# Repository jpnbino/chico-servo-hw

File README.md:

# Chico - HW #

This is a fully working board which you may wanna use as reference or may clone and customize to your needs. The board was designed to an specific project which required ADC, PWM, SERIAL, and I/O connection.

Example firmware [**here**](https://bitbucket.org/jpnbino/fw_palhaservo/src/master/).

## PCB ##

### Board details ###

|  Item           |Description |
|-----------------|------------|
| Core            | PIC16LF1824|
| Input Voltage (Vin)   |  4.75V ≤ Vin ≤ 10V    |
| Board Size      | 16.5mm x 31mm|
| User LED        | 1            |

### The project ###

* Quick summary

  * The project now lives in **KiCad 10** (`kicad/`). The original Altium Designer sources are **frozen** in `altium/` and are no longer maintained.

* Version

  * V1I1 - Initial.

### Video ####

I recorded this video when I was building the first prototype.

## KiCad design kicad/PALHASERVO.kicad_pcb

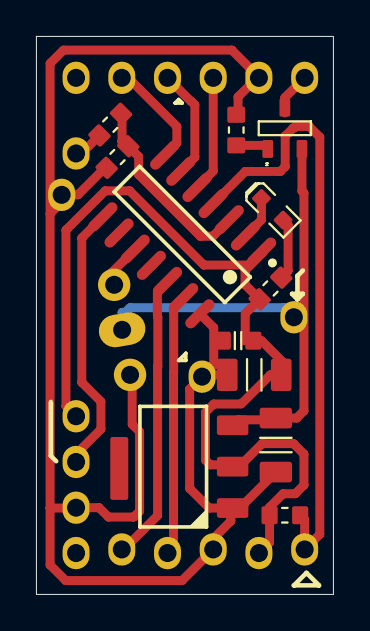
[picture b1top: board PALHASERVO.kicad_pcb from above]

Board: 2 copper layers, 16.5 x 31.0 mm, 20 parts (0 on the bottom side), 17 nets.

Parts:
C1: 100n; CAPC1608X90N
C2, C3: 10µ; CAPC3216X180N
J2: pickit3; CONN_ICSP
LED1: RED; LED-0603-RED
P1, P3: 3; PAD_PTH 3 vias
P2: 6; PAD_PTH 6 VIAS
P4, P5, P6, P7: 1; PAD_PTH
Q2: BSS123; SOT23-3
R3, R5, R6, R7: 10K; RESC1608X55N
R4: 1K; RESC1608X55N
U1: PIC16LF1824-I/SL; MCHP-SOIC-SL14_N
U2: 3V3, 1A; SOT223

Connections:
ADC_POT: P3.2, U1.8
GND: C1.1, C2.2, C3.2, J2.3, P1.1, P2.2, P3.3, P5.1, P7.1, R5.2, R6.2, U1.14, U2.1
HC_05_KEY: P2.5, U1.7
HC_05_POWER_ON: Q2.1, R6.1
HC_05_VCC5V0: P2.1, Q2.3
ICSPCLK: J2.5, U1.12
ICSPDAT: J2.4, U1.13
LED_LOW_BATT: LED1.K, U1.2
MCU_RX: P2.3, U1.5
MCU_TX: P2.4, U1.6
NetLED1_A: LED1.A, R4.2
SERVO_PWM: P1.3, U1.10
VCC3V3: C1.2, C3.1, J2.2, P3.1, R4.1, R7.1, U1.1, U2.2
VCC5V0: C2.1, P1.2, P4.1, Q2.2, U2.3
V_BAT: P6.1, R3.1
V_BAT_ADC: R3.2, R5.1, U1.3
~MCLR: J2.1, R7.2, U1.4

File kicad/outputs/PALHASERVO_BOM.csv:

"Reference","Value","Footprint","QUANTITY"
"C1","100n","chico_servo:CAPC1608X90N","1"
"C2,C3","10µ","chico_servo:CAPC3216X180N","2"
"J2","pickit3","chico_servo:CONN_ICSP","1"
"LED1","RED","chico_servo:LED-0603-RED","1"
"P1,P3","3","chico_servo:PAD_PTH 3 vias","2"
"P2","6","chico_servo:PAD_PTH 6 VIAS","1"
"P4-P7","1","chico_servo:PAD_PTH","4"
"Q2","BSS123","chico_servo:SOT23-3","1"
"R3,R5-R7","10K","chico_servo:RESC1608X55N","4"
"R4","1K","chico_servo:RESC1608X55N","1"
"U1","PIC16LF1824-I/SL","chico_servo:MCHP-SOIC-SL14_N","1"
"U2","3V3, 1A","chico_servo:SOT223","1"

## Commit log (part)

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2018-04-08 README.md edited online with Bitbucket
2018-04-09 Commit inicial
2018-04-11 Circuito MCU, SERVO, HC - 05 feitos, mas não revisados
2018-04-12 Floor planning em andamento
2018-04-13 Roteamento em andamento. Modificações no esquema elétrico
2018-04-13 Roteamento em adicionado resistir de pull-up do master clear. pinos no esquema elétrico trocados.
2018-04-13 Roteamento em andamento.
2018-04-13 Placa enviada para a produção.
2025-08-20 Add PCB images to readme
